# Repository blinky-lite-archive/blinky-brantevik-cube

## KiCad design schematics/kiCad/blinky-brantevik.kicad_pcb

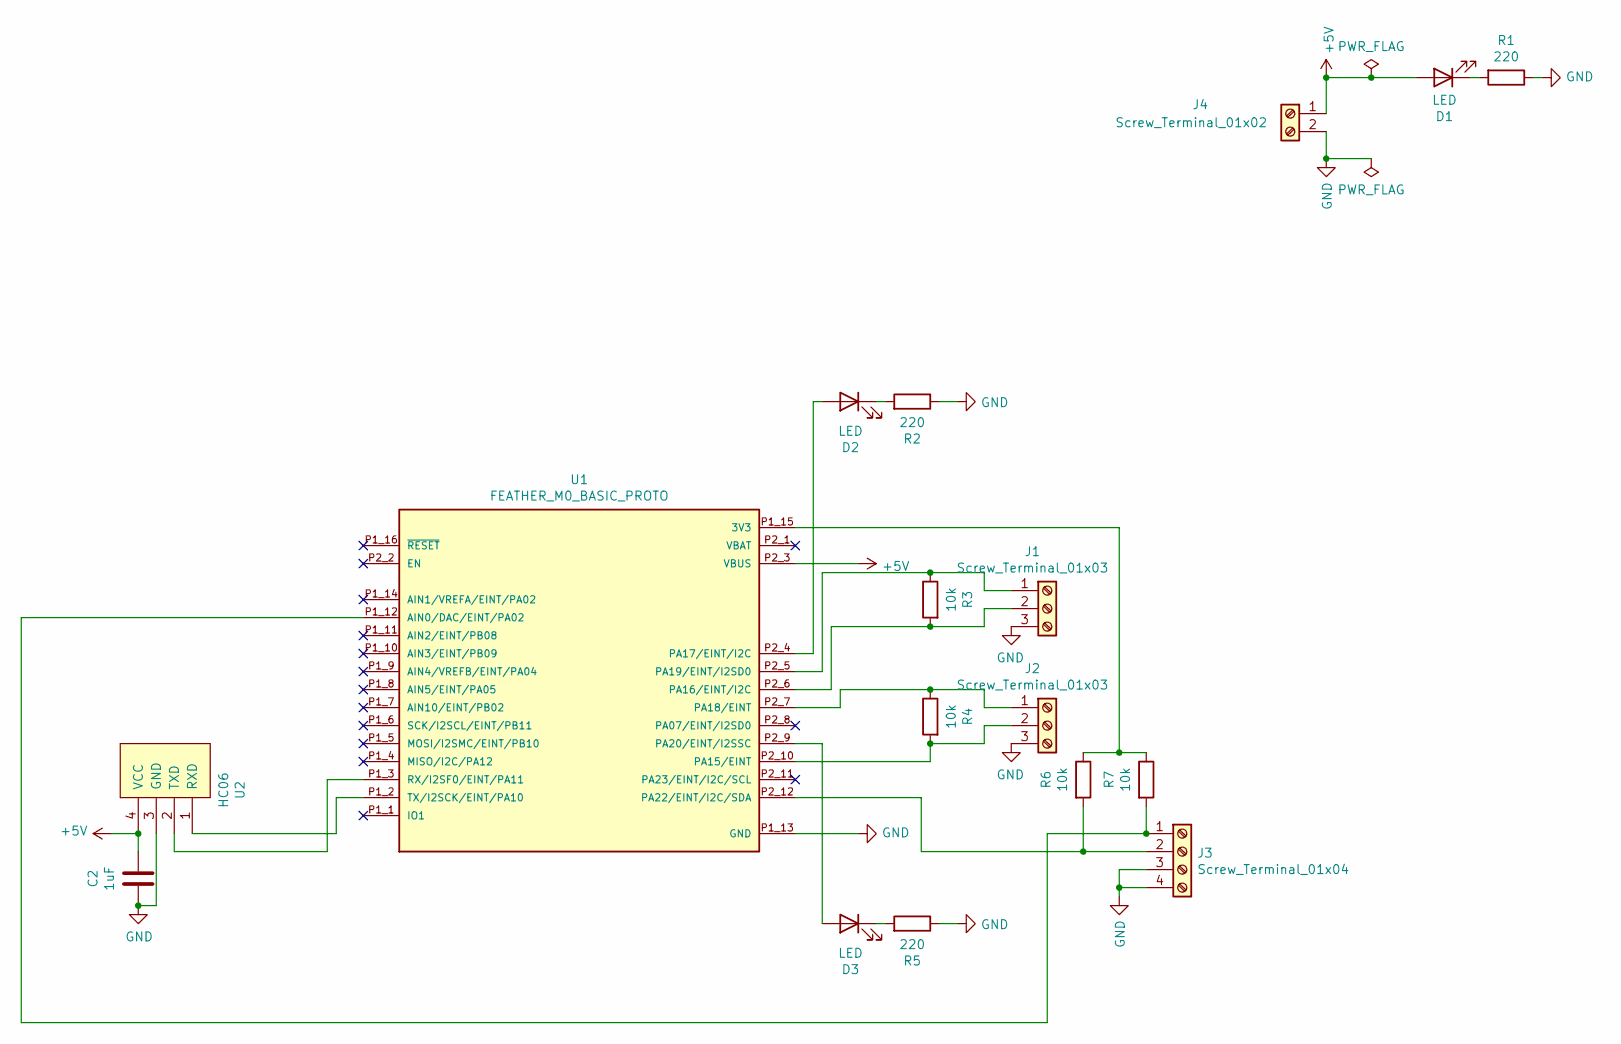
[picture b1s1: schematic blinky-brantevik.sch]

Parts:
C2: 1uF; C_1206_3216Metric_Pad1.33x1.80mm_HandSolder
D1, D2, D3: LED; LED_D5.0mm
J1, J2: Screw_Terminal_01x03; TerminalBlock_bornier-3_P5.08mm
J3: Screw_Terminal_01x04; TerminalBlock_bornier-4_P5.08mm
J4: Screw_Terminal_01x02; TerminalBlock_bornier-2_P5.08mm
R1, R2, R5: 220; R_1206_3216Metric_Pad1.30x1.75mm_HandSolder
R3, R4, R6, R7: 10k; R_1206_3216Metric_Pad1.30x1.75mm_HandSolder
U1: FEATHER_M0_BASIC_PROTO; MODULE_FEATHER_M0_BASIC_PROTO
U2: HC06

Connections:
+5V: C2.1, D1.2 (A), J4.1, U1.P2_3 (VBUS), U2.4 (VCC)
GND: C2.2, J1.3, J2.3, J3.3, J3.4, J4.2, R1.1, R2.1, R5.1, U1.P1_13 (GND), U2.3 (GND)
unnamed: D1.1 (K), R1.2
unnamed: D2.1 (K), R2.2
unnamed: D2.2 (A), U1.P2_4 (PA17/EINT/I2C)
unnamed: D3.1 (K), R5.2
unnamed: D3.2 (A), U1.P2_9 (PA20/EINT/I2SSC)
unnamed: J1.1, R3.1, U1.P2_5 (PA19/EINT/I2SD0)
unnamed: J1.2, R3.2, U1.P2_6 (PA16/EINT/I2C)
unnamed: J2.1, R4.1, U1.P2_7 (PA18/EINT)
unnamed: J2.2, R4.2, U1.P2_10 (PA15/EINT)
unnamed: J3.1, R7.2, U1.P1_12 (AIN0/DAC/EINT/PA02)
unnamed: J3.2, R6.2, U1.P2_12 (PA22/EINT/I2C/SDA)
unnamed: R6.1, R7.1, U1.P1_15 (3V3)
unnamed: U1.P1_2 (TX/I2SCK/EINT/PA10), U2.1 (RXD)
unnamed: U1.P1_3 (RX/I2SF0/EINT/PA11), U2.2 (TXD)

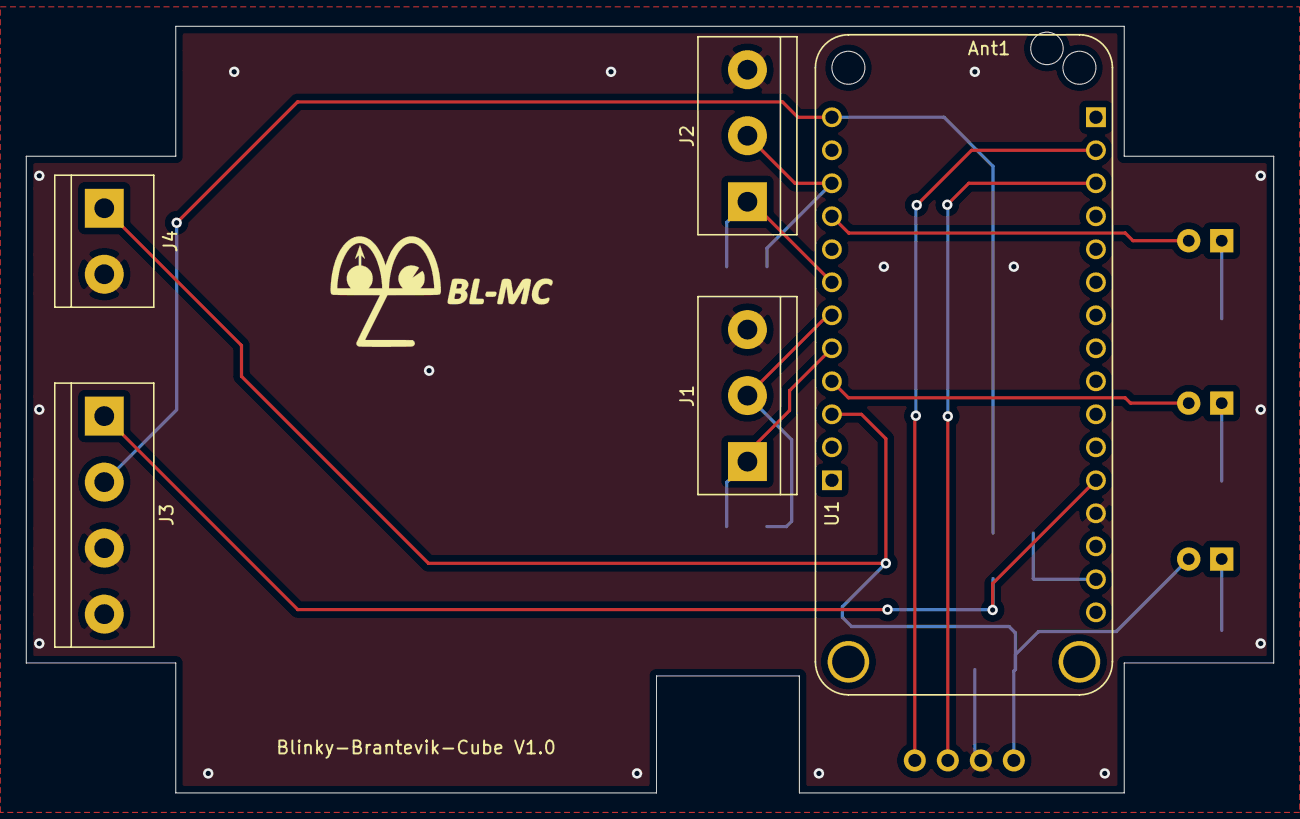
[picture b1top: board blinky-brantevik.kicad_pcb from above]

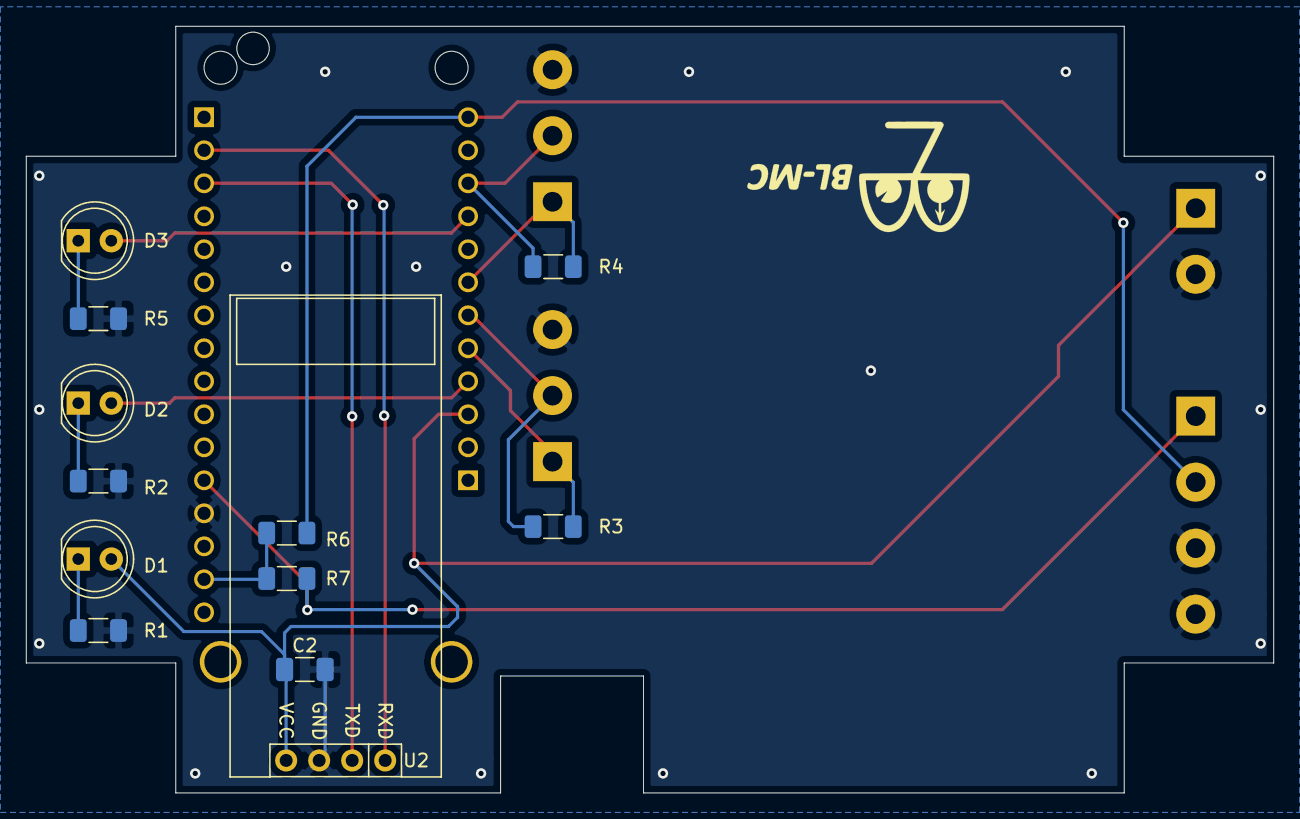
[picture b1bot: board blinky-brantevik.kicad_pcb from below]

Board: 2 copper layers, 96.0 x 59.0 mm, 18 parts (12 on the bottom side), 16 nets.

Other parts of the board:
Ant1: MountingHole_2.5mm

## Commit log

2021-07-02 first commit of two devices
2021-07-16 started new schematic
2021-07-16 more schem layout
2021-07-18 ew brantevik cube link file
2021-07-18 pcb complete
2021-07-21 added cubeWindLinkCode
2021-07-23 cubeWaterLevelCode
